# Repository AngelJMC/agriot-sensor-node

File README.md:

# AGRIOT LoraWAN sensor node

The aim of this project is to provide an Open Source hardware/software platform for the rapid and low-cost development of LoRaWAN sensor nodes. It consists of an [Arduino Pro Mini][4] module, a LoRa [RMF95W][5] communications module, a Buck DC-DC converter and a few components to simplify connection to different sensors.

## Table of contents
- [AGRIOT LoraWAN sensor Node](#agriot-lorawan-sensor-node)
  - [General info](#general-info)
  - [Table of contents](#table-of-contents)
  - [Features](#features)
    - [Hardware](#hardware)
    - [LoRaWAN Features](#lorawan-features)
    - [List of supported sensors](#list-of-supported-sensors)
  - [Get the source code](#get-the-source-code)
    - [Directory Structure](#directory-structure)
  - [Firmware](#firmware)
    - [How to add new sensor support](#how-to-add-new-sensor-support)
  - [Command Line Interface](#command-line-interface)
    - [Commands](#commands)
  - [Connect your Device to LoRaWAN - The Things Network.](#connect-your-device-to-lorawan---the-things-network)
    - [Get your Device EUI](#get-your-device-eui)
    - [Activate your Device](#activate-your-device)
  - [Hardware](#hardware-1)
    - [PCB BOM](#pcb-bom)
  - [Node Examples](#node-examples)

## Features
### Hardware
 * 5-24v Power supply through a screw terminal block.
 * 2 GPIOS accessible from screw terminal blocks, one of them with interrupt.
 * 1 IC2 interface in the botton layer, with soldering pad.
 * 4 Analog inputs in the top layer, with soldering pad.
 * A switch to force the sending of LoRaWAN messages.
### LoRaWAN Features
* [OTAA activation][7]. It is not necessary to add the OTAA activation keys in the code. They are stored in the EEPROM and the configuration is done from the serial port. 
* [Adaptative Data Rate][6] according to the SNR of periodical downlink messages.
* Using [Arduino-LMIC lowpower library][8], a modified version of Arduino-LMIC to work with the low-power modes of the Atmega328P microcontroller.
### List of supported sensors
* DHT series of low-cost temperature/humidity sensors.
* DS18S20, DS18B20, DS1822 temperature sensor.
* GPS with NMEA Standar.
* ADC121 Analog-to-digital converter with I2C interface.
    
## Get the source code
Download repository and update submodules:

```
$ git clone https://github.com/AngelJMC/agriot-sensor-node.git
$ cd agriot-sensor-node
$ git submodule update --init --recursive
```

### Directory Structure

    .
    ├── docs          # Documentation files
    ├── firmware      # FW source code (Visual Studio Code)
    ├── hardware      # HW design files (Kicad)

## Firmware
If you want to modify the source code or program your devices, it is highly recommended to use [Visual Studio Code][2] and the [Platformio][3] plugin. Just open the "firmware" directory with Visual Studio Code and the whole project will be ready for use.
### How to add new sensor support

You must create a new .cpp file in which you implement the communication routines with the sensor. If you use the following scheme you will only have to add the communication with the sensor.  The sensors_update() function is executed periodically and once the sensor acquisition is finished the data is sent by the LoRaWAN communication layer.

~~~
#ifdef SENS_SENSORNAME
#include "protocol.h"
#include "sensors.h"
#include <CayenneLPP.h>

/* Schedule sensore measurement every this senconds */
#define SENSOR_INTERVAL (5*60) //seconds

static osjob_t sensjob;
CayenneLPP lpp(51);

static void sensors_update( osjob_t* j ) {
    os_avoidSleep();

    /*TO-BE Implemented -- Read sensor*/
    float t = readYourSensor();

    /* Update Data Frame using Cayennne Library */
    lpp.reset();
    lpp.addTemperature(1, t); /*Change according your sensor*/
    protocol_updateDataFrame( lpp.getBuffer(), lpp.getSize() );

    /* Schedule next sensor reading*/
    os_setTimedCallback( &sensjob, os_getTime() + sec2osticks(SENSOR_INTERVAL), sensors_update );
    Serial.flush();
    os_acceptSleep();
}

void sensors_init( ) {

    /*TO-BE Implemented -- Init sensor*/
    initYourSensor();

    /*Schedule the first sensor reading*/
    os_setTimedCallback(&sensjob, os_getTime() + sec2osticks(10), sensors_update);
}

#endif

~~~

To compile the code for this new sensor, you will have to add to the platformio.ini configuration file a new [build environment][1].

~~~
[env:pro8MHzatmega328_SENSORNAME]
platform = atmelavr
board = pro8MHzatmega328
framework = arduino
build_flags = -DSENS_SENSORNAME
~~~

Now you will be able to select the build environment from the Visual Studio Code.

## Command Line Interface

The device configuration is done through the command line interface (CLI) implemented in the device.

First, connect your device to the Arduino Serial Monitor over USB. Since the Arduino Pro Mini does not have an on-board FTDI chip, you will need to use a USB-TTL adapter. Set the baud rate to 9600 and open the serial port to establish connection. IMPORTANT: To reduce the device power consumption, the serial interface is only available for 10 minutes after the device power-up.

### Commands

Command ID| Type   | Description 
:--------:|--------|:----------
  D       | R      |  DEVEUI -  Unique device identifier.
  E       | R/W    |  APPEUI -  Unique identifier of the application.    
  K       | R/W    |  APPKEY -  Used in OTAA to generate session keys. 

## Connect your Device to LoRaWAN - The Things Network.

To use the default Over The Air Activation (OTAA) you will need to register your device with its Device EUI

### Get your Device EUI

The Device EUI is a unique address provided by the Atmega328P microcontroller. To retrieve this, type in the serial console:

> D    

Go to The Things Network and open the application to which you wish to add a device and click register device.
        
  * For Device ID, choose a - for this application - unique ID of lower case, alphanumeric characters and nonconsecutive - and _.
  * For Device EUI, copy-paste the one you retrieved from your device.
  * Leave the App Key to be generated.
  * For App EUI, select the generated EUI from the list.

### Activate your Device

Now that we have registered the device, we can activate the connection from our device itself. Activation means that the device will use the generated App Key to negotiate session keys for further communication. 

Go to Device Overview and copy the 8-byte Application EUI. Now, you have to send the "E" command with the value obtained through the serial port of the device:

> E:70B3D57ED0038147

Repeat the same process to send the 16 byte Application key:

> K:7B4F7BC85D064898DB39214D7607440E

Now, restart the device and it will automatically register to the network.

Session keys are not stored in non-volatile memory so they are renegotiated each time the device is powered on. This behavior is not the most appropriate, and will be reviewed in future versions.

## Hardware

Getting the gerbers for PCB fabrication [here]([hardware/gerbers](https://github.com/AngelJMC/agriot-sensor-node/tree/master/hardware/gerbers)).

### PCB BOM

| Name  | Anmount | Description |
| ------------- | ------------- | ------------- |
| [Arduino Pro Mini][20]          | 1  | Pro Mini Armega328P 3,3V 8MHz|
| [RFM95W][21]                    | 1  | RFM95W 868-915MHz LoRa SX1276 transceiver |
| [DC-DC Buck][22]                | 1  | 3.3V Fixed output, Input 5v-24v |
| Resistor 2.2k                   | 1  | 2.2K SMD resistor 0805|
| Resistor 4.7k                   | 3  | 4.7K SMD resistor 0805|
| Capacitor 4.7 uF/6.3 v          | 1  | 4.7 uF SMD capacitor 0805 |
| SMD LED                       | 1  | LED SMD 0850 |
| [Switch DIP][3]                 | 1  | Switch 4 PIN Metal SMD  |
| [Screw Terminal 01x03][24]      | 2  | 3P - Pitch 3.5/3.96mm Screw PCB Terminal Block Connector |
| [Screw Terminal 01x02][24]      | 1  | 2P - Pitch 3.5/3.96mm Screw PCB Terminal Block Connector |
| [Connector U.FL-R-SMT ][25]     | 1  |  Connector U.FL-R-SMT |
| [Antenna 3dbi RP-SMA][26]       | 1  |  Antenna 3dbi RP-SMA Connector + 21cm SMA Male/u.FL Pigtail Cable |

[20]:https://es.aliexpress.com/item/32341751484.html?spm=a2g0s.9042311.0.0.274263c0KXTWNh
[21]:https://es.aliexpress.com/item/32811523237.html?spm=a2g0s.9042311.0.0.274263c0h3imgq
[22]:https://es.aliexpress.com/item/32742116421.html?spm=a2g0s.9042311.0.0.274263c0h3imgq
[23]:https://www.aliexpress.com/item/32989610390.html?spm=a2g0s.9042311.0.0.274263c02c3pDo
[24]:https://es.aliexpress.com/item/32868442939.html?spm=a2g0s.9042311.0.0.274263c0HmLjas
[25]:https://es.aliexpress.com/item/32833564737.html?spm=a2g0s.9042311.0.0.274263c0HmLjas
[26]:https://www.aliexpress.com/item/32977287261.html?spm=a2g0s.9042311.0.0.274263c0KXTWNh

## Node Examples

[1]: https://docs.platformio.org/en/latest/projectconf/section_env.html
[2]: https://code.visualstudio.com/
[3]: https://platformio.org/
[4]:https://learn.sparkfun.com/tutorials/using-the-arduino-pro-mini-33v/all.pdf
[5]:http://www.anarduino.com/docs/RFM95_96_97_98W.pdf
[6]:https://www.thethingsnetwork.org/docs/lorawan/adaptive-data-rate.html
[7]:https://www.thethingsnetwork.org/docs/devices/registration.html
[8]:https://github.com/AngelJMC/arduino-lmic-lowpower

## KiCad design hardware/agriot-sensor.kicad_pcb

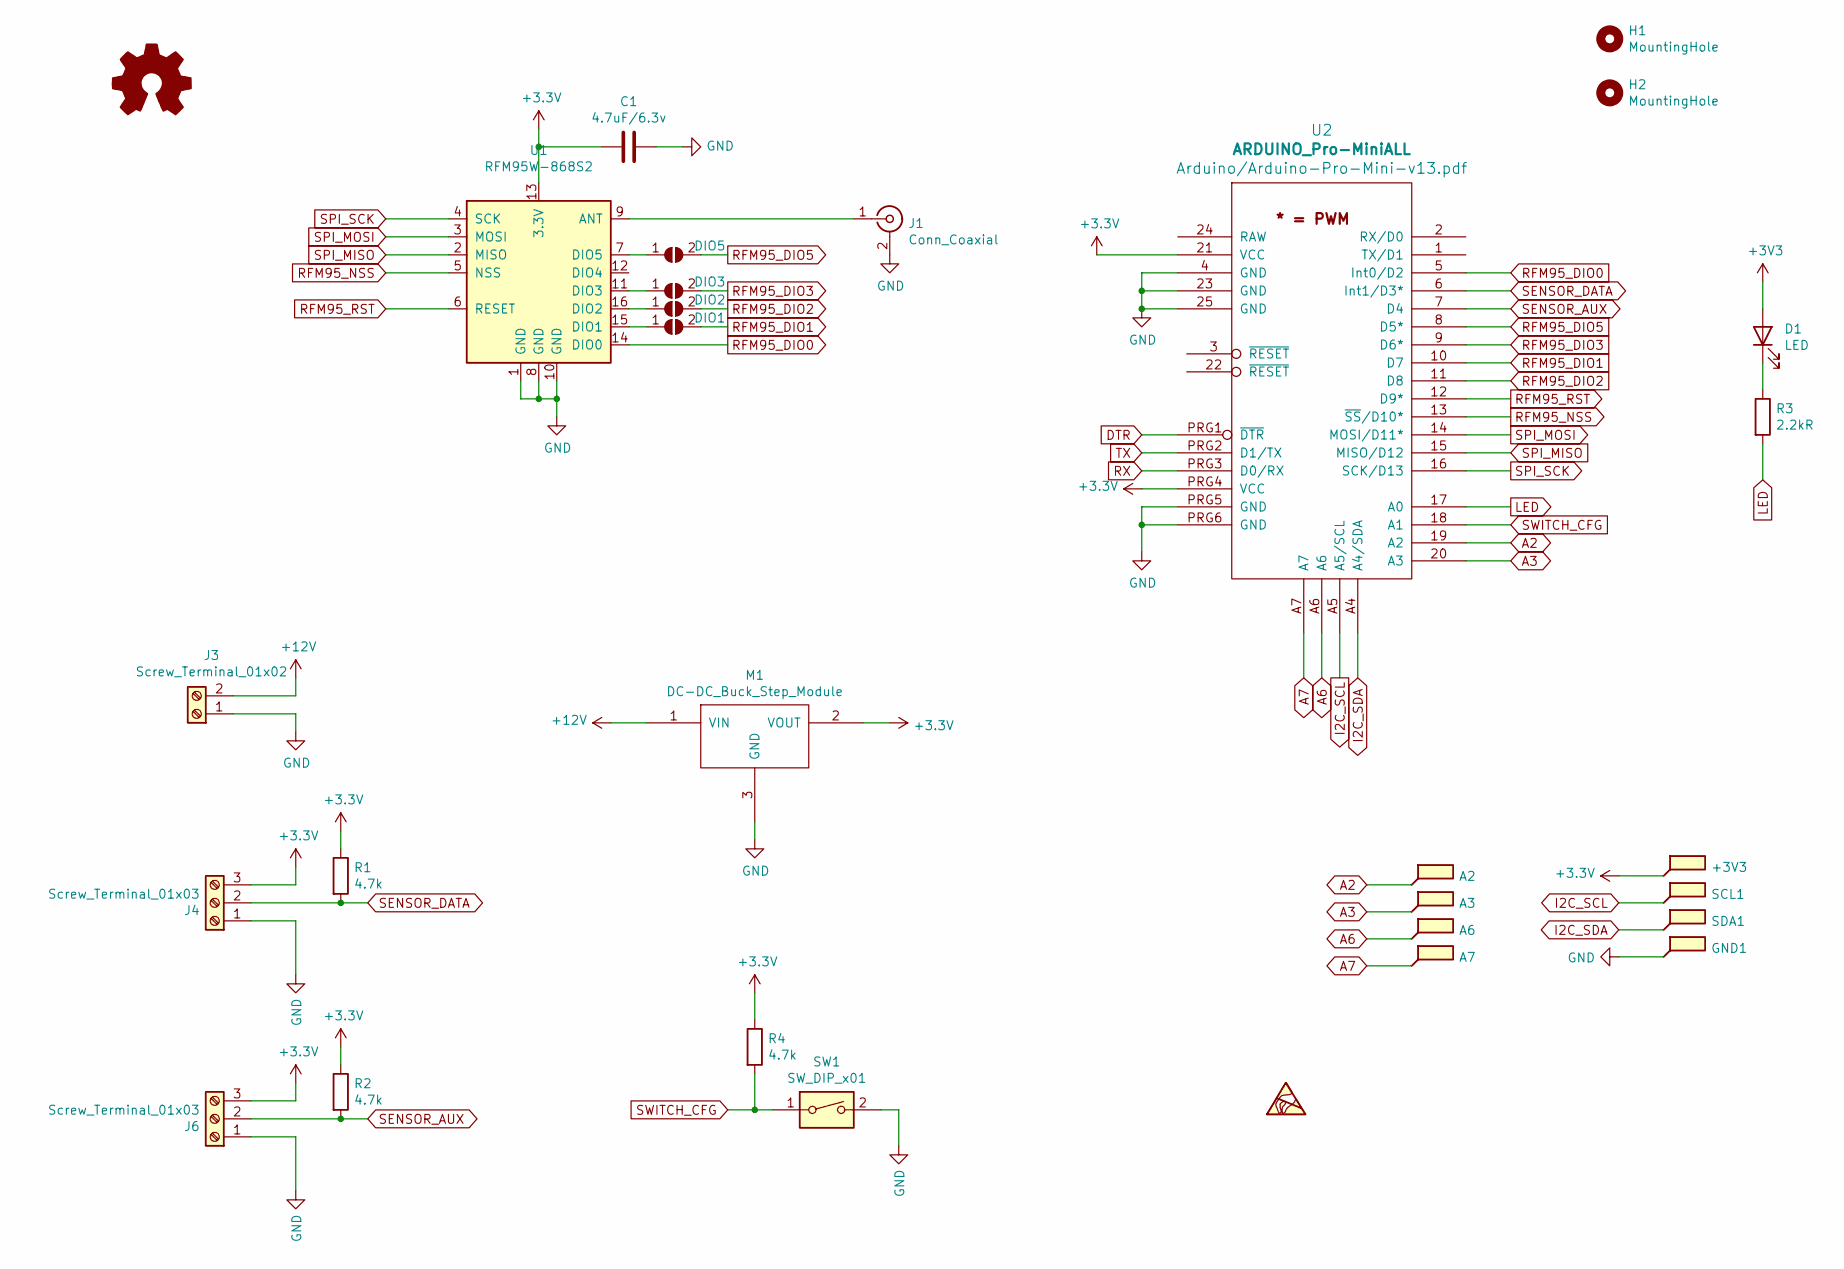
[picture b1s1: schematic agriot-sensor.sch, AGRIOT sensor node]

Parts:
+3V3: +3v3; TestPoint_Pad_1.5x1.5mm
A2: +3v3; TestPoint_Pad_1.5x1.5mm
A3: SCL; TestPoint_Pad_1.5x1.5mm
A6: SDA; TestPoint_Pad_1.5x1.5mm
A7: GND; TestPoint_Pad_1.5x1.5mm
C1: 4.7uF/6.3v; C_0805_2012Metric
D1: LED; LED_0805_2012Metric
DIO1, DIO2, DIO3, DIO5: SolderJumper_2_Open; SolderJumper-2_P1.3mm_Open_RoundedPad1.0x1.5mm
GND1: GND; TestPoint_Pad_1.5x1.5mm
H1, H2: MountingHole; MountingHole_3.2mm_M3
J1: Conn_Coaxial; U.FL_Molex_MCRF_73412-0110_Vertical
J3: Screw_Terminal_01x02; TerminalBlock_4Ucon_1x02_P3.50mm_Horizontal
J4, J6: Screw_Terminal_01x03; TerminalBlock_4Ucon_1x03_P3.50mm_Horizontal
M1: DC-DC_Buck_Step_Module
R1, R2, R4: 4.7k; R_0805_2012Metric
R3: 2.2kR; R_0805_2012Metric
SCL1: SCL; TestPoint_Pad_1.5x1.5mm
SDA1: SDA; TestPoint_Pad_1.5x1.5mm
SW1: SW_DIP_x01; SW_Push_1P1T_NO_CK_KSC6xxJ
U1: RFM95W-868S2; HOPERF_RFM9XW_SMD
U2: ARDUINO_Pro-MiniALL; ARDUINO_Pro-MiniALLB_Aliexpress

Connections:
+12V: J3.2, M1.1 (VIN)
A2: A2.1, U2.19 (A2)
A3: A3.1, U2.20 (A3)
A6: A6.1, U2.A6
A7: A7.1, U2.A7
DTR: U2.PRG1 (~DTR)
GND: C1.1, GND1.1, J1.2 (Ext), J3.1, J4.1, J6.1, M1.3 (GND), SW1.2, U1.1 (GND), U1.8 (GND), U1.10 (GND), U2.4 (GND), U2.23 (GND), U2.25 (GND), U2.PRG5 (GND), U2.PRG6 (GND)
I2C_SCL: SCL1.1, U2.A5 (A5/SCL)
I2C_SDA: SDA1.1, U2.A4 (A4/SDA)
LED: R3.2, U2.17 (A0)
unnamed: D1.1 (K), R3.1
unnamed: DIO1.1 (A), U1.15 (DIO1)
unnamed: DIO2.1 (A), U1.16 (DIO2)
unnamed: DIO3.1 (A), U1.11 (DIO3)
unnamed: DIO5.1 (A), U1.7 (DIO5)
unnamed: J1.1 (In), U1.9 (ANT)
RFM95_DIO0: U1.14 (DIO0), U2.5 (Int0/D2)
RFM95_DIO1: DIO1.2 (B), U2.10 (D7)
RFM95_DIO2: DIO2.2 (B), U2.11 (D8)
RFM95_DIO3: DIO3.2 (B), U2.9 (D6*)
RFM95_DIO5: DIO5.2 (B), U2.8 (D5*)
RFM95_NSS: U1.5 (NSS), U2.13 (~SS~/D10*)
RFM95_RST: U1.6 (RESET), U2.12 (D9*)
RX: U2.PRG3 (D0/RX)
SENSOR_AUX: J6.2, R2.2, U2.7 (D4)
SENSOR_DATA: J4.2, R1.2, U2.6 (Int1/D3*)
SPI_MISO: U1.2 (MISO), U2.15 (MISO/D12)
SPI_MOSI: U1.3 (MOSI), U2.14 (MOSI/D11*)
SPI_SCK: U1.4 (SCK), U2.16 (SCK/D13)
SWITCH_CFG: R4.2, SW1.1, U2.18 (A1)
TX: U2.PRG2 (D1/TX)

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
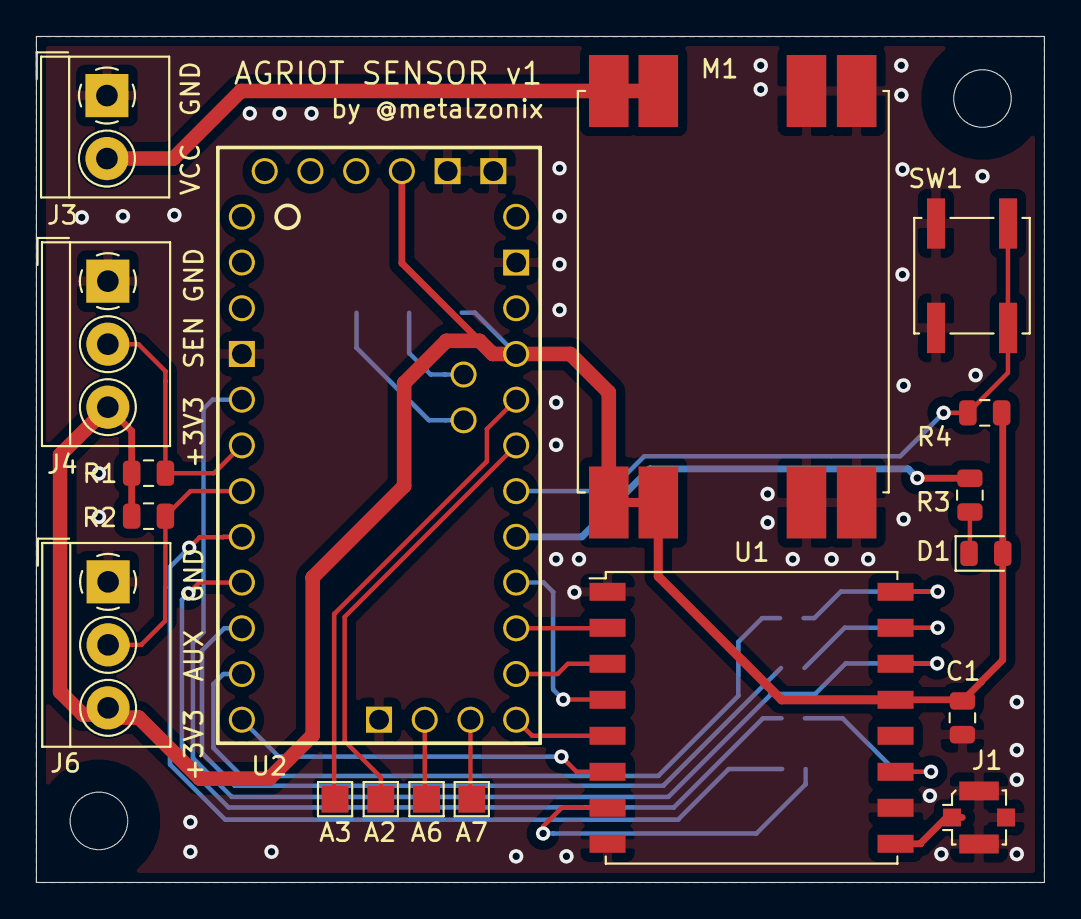
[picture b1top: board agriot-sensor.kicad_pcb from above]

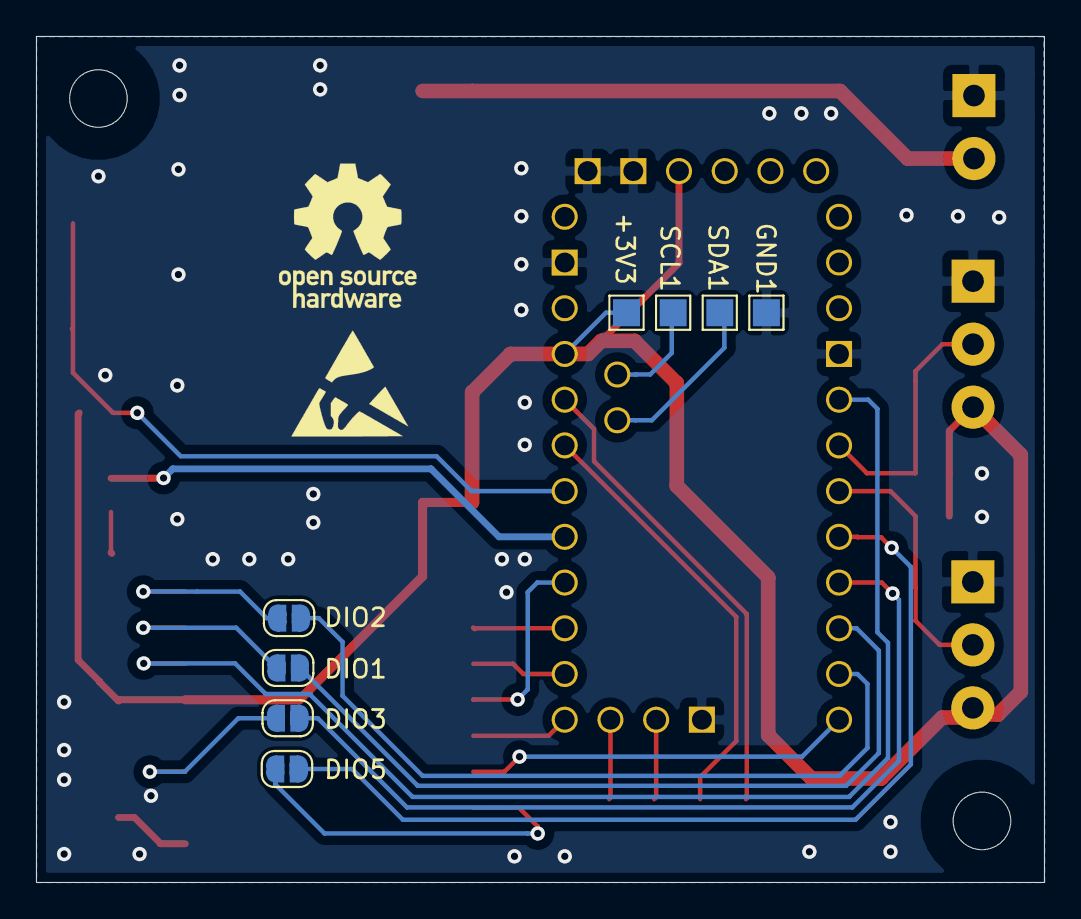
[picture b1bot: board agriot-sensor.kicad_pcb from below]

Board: 2 copper layers, 56.0 x 47.0 mm, 28 parts (8 on the bottom side), 29 nets.

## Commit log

2019-12-22 Add all hardware design file for Kicad
2019-12-22 Add a basic firmware version
2019-12-22 WIP - Refactor main file
2019-12-24 Work around main.cpp. Add support for DHT22 and DS18B20 sensors.
2020-03-03 Add new macros to selec sensor type, tx interval and sampling time.
2020-07-14 Using git submodules to add dependences.
2020-07-24 WIP - Add command line interpreter
2020-07-24 Test travis
2020-07-24 Update travis CI
2020-07-24 Testing travis...
2020-08-11 Code structure has been improved
2020-08-19 Bug fixing and other minors changes
2020-09-26 Change Activation by Personalization(ABP) to Over-the-Air Activation (OTAA)
    Over-the-Air Activation (OTAA) is the preferred and most secure way to
    connect with The Things Network. Devices perform a join-procedure with
    the network, during which a dynamic DevAddr is assigned and security
    keys are negotiated with the device.
2020-09-26 Add support for the TM5 Moisture - Temperature Sensor
2020-09-26 Fix issues on SDISerial library
2020-11-02 Several improvements in the code style. Reduction of memory consumption.
2020-11-02 Add new sensor support, ADC121 driver to read the Capative Soil Moisture analog sensor
2020-11-02 Update the hardware design files
2020-11-02 Add AsyncSerial fork submodule
2020-11-02 Update AsyncSerial submodule version
2020-11-02 Call AsyncSerial functions from the run-time enviroment LMIC.
2020-11-02 Create new module to manage the configuration parameters
2020-11-02 Add cfg file.
2020-11-08 Improve command line interface.
2020-11-08 Use Adaptative Data Rate (ADR), fix bug with the lmic library when use this feature.
2020-11-11 Minor changes to reduce the use of the Flash memory .
2020-11-24 Bug fixing related to last changes in command line interface.
2020-11-28 Improvements to reduce power requirements. When the cpu is idle waiting for the execution of the next job, it is put in power-down mode. - Modified lmic layer. - Usage of low-power library.
2020-11-29 Update hardware schematic
2020-12-09 The reading of the sensors and data sending have been synchronized.
2020-12-09 Added support for ublox NEO-6m gps.
    It should be compatible with other GPS's that use the NMEA standard and
    transmit over USART.
2020-12-10 Update hardware files
2020-12-10 Add the project kicad libraries to repository
2020-12-10 Update kicad project files
2020-12-10 Remove unused kicad files.
2020-12-10 Added hardware license
2020-12-10 Add new gitignore in root.
2020-12-12 Modified repository name
2020-12-12 Add option to use also CayenneLPP procotol to send location.
2020-12-19 Only use OTTA for first time to get the session keys.
    The first time, the device will connect over OTAA. TTN will return
    fresh network session key and an application session key that should be
    used for the next connection (after reset). Therefore the keys are saved
    in non-volitile storage after joining in EEPROM memory. Every 100
    messages, the keys and sequency number are save in EEPROM.
2021-01-23 Update documentation
2021-04-10 Added new build flavour TEMP_MOISTURE
    Implements temperature and soil moisture probe readout
2023-05-21 Added weather station device: Air Temperature and Humidity + Soil temp + Soil moisture
2025-10-26 Added support for HX711, a precision 24-bit analog-to-digital converter (ADC) designed for weigh scales
